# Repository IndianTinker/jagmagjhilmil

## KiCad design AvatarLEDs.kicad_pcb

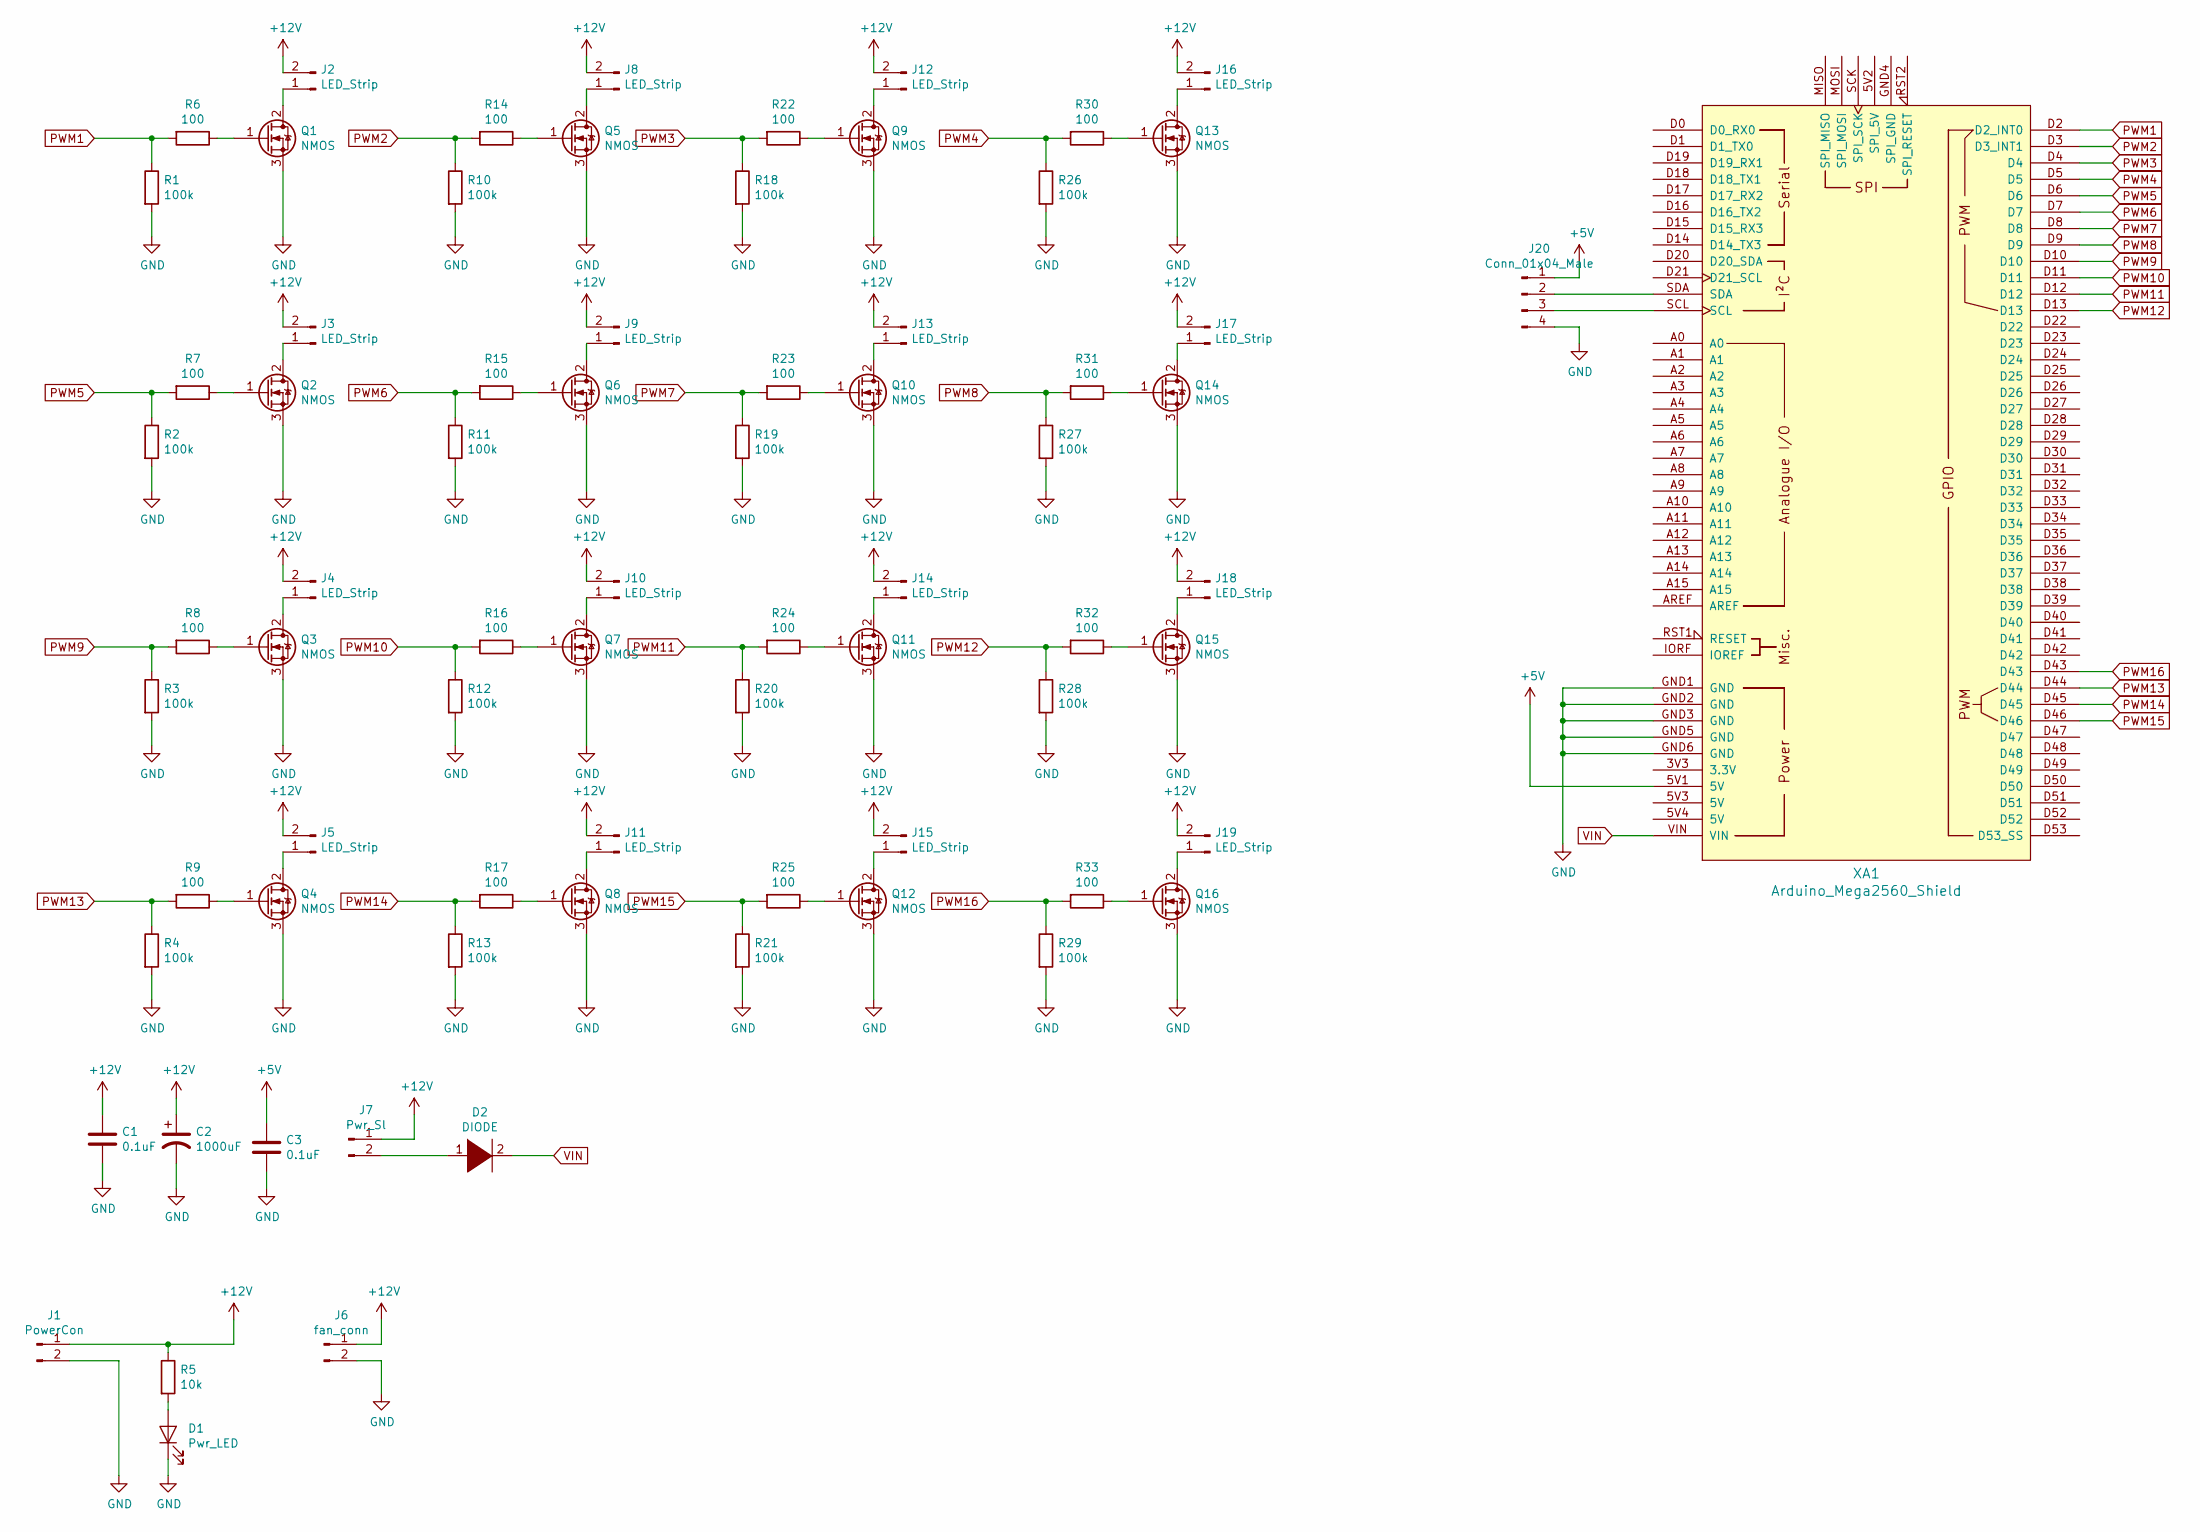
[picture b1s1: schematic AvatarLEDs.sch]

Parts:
C1, C3: 0.1uF; C_0805_2012Metric_Pad1.15x1.40mm_HandSolder
C2: 1000uF; CP_Elec_5x3
D1: Pwr_LED; LED_D3.0mm_FlatTop
D2: DIODE; Diode_Bridge_Round_D9.0mm
J1: PowerCon; TerminalBlock_Phoenix_MKDS-1,5-2_1x02_P5.00mm_Horizontal
J2, J3, J4, J5, J8, J9, J10, J11, J12, J13, J14, J15, J16, J17, J18, J19: LED_Strip; TerminalBlock_Phoenix_MKDS-1,5-2_1x02_P5.00mm_Horizontal
J6: fan_conn; JST_EH_B02B-EH-A_1x02_P2.50mm_Vertical
J7: Pwr_Sl; JST_EH_B02B-EH-A_1x02_P2.50mm_Vertical
J20: Conn_01x04_Male; JST_EH_B04B-EH-A_1x04_P2.50mm_Vertical
Q1, Q2, Q3, Q4, Q5, Q6, Q7, Q8, Q9, Q10, Q11, Q12, Q13, Q14, Q15, Q16: NMOS; TO-220-3_Vertical
R1, R2, R3, R4, R10, R11, R12, R13, R18, R19, R20, R21, R26, R27, R28, R29: 100k; R_1206_3216Metric_Pad1.42x1.75mm_HandSolder
R5: 10k; R_1206_3216Metric_Pad1.42x1.75mm_HandSolder
R6, R7, R8, R9, R14, R15, R16, R17, R22, R23, R24, R25, R30, R31, R32, R33: 100; R_1206_3216Metric_Pad1.42x1.75mm_HandSolder
XA1: Arduino_Mega2560_Shield

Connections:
+5V: C3.1, J20.1, XA1.5V1 (5V)
+12V: C1.1, C2.1, J1.1, J2.2, J3.2, J4.2, J5.2, J6.1, J7.1, J8.2, J9.2, J10.2, J11.2, J12.2, J13.2, J14.2, J15.2, J16.2, J17.2, J18.2, J19.2, R5.1
GND: C1.2, C2.2, C3.2, D1.1 (K), J1.2, J6.2, J20.4, Q1.3 (S), Q2.3 (S), Q3.3 (S), Q4.3 (S), Q5.3 (S), Q6.3 (S), Q7.3 (S), Q8.3 (S), Q9.3 (S), Q10.3 (S), Q11.3 (S), Q12.3 (S), Q13.3 (S), Q14.3 (S), Q15.3 (S), Q16.3 (S), R1.2, R2.2, R3.2, R4.2, R10.2, R11.2, R12.2, R13.2, R18.2, R19.2, R20.2, R21.2, R26.2, R27.2, R28.2, R29.2, XA1.GND1 (GND), XA1.GND2 (GND), XA1.GND3 (GND), XA1.GND5 (GND), XA1.GND6 (GND)
unnamed: D1.2 (A), R5.2
unnamed: D2.1 (K), J7.2
unnamed: J2.1, Q1.2 (D)
unnamed: J3.1, Q2.2 (D)
unnamed: J4.1, Q3.2 (D)
unnamed: J5.1, Q4.2 (D)
unnamed: J8.1, Q5.2 (D)
unnamed: J9.1, Q6.2 (D)
unnamed: J10.1, Q7.2 (D)
unnamed: J11.1, Q8.2 (D)
unnamed: J12.1, Q9.2 (D)
unnamed: J13.1, Q10.2 (D)
unnamed: J14.1, Q11.2 (D)
unnamed: J15.1, Q12.2 (D)
unnamed: J16.1, Q13.2 (D)
unnamed: J17.1, Q14.2 (D)
unnamed: J18.1, Q15.2 (D)
unnamed: J19.1, Q16.2 (D)
unnamed: J20.2, XA1.SDA
unnamed: J20.3, XA1.SCL
unnamed: Q1.1 (G), R6.1
unnamed: Q2.1 (G), R7.1
unnamed: Q3.1 (G), R8.1
unnamed: Q4.1 (G), R9.1
unnamed: Q5.1 (G), R14.1
unnamed: Q6.1 (G), R15.1
unnamed: Q7.1 (G), R16.1
unnamed: Q8.1 (G), R17.1
unnamed: Q9.1 (G), R22.1
unnamed: Q10.1 (G), R23.1
unnamed: Q11.1 (G), R24.1
unnamed: Q12.1 (G), R25.1
unnamed: Q13.1 (G), R30.1
unnamed: Q14.1 (G), R31.1
unnamed: Q15.1 (G), R32.1
unnamed: Q16.1 (G), R33.1
PWM1: R1.1, R6.2, XA1.D2 (D2_INT0)
PWM2: R10.1, R14.2, XA1.D3 (D3_INT1)
PWM3: R18.1, R22.2, XA1.D4
PWM4: R26.1, R30.2, XA1.D5
PWM5: R2.1, R7.2, XA1.D6
PWM6: R11.1, R15.2, XA1.D7
PWM7: R19.1, R23.2, XA1.D8
PWM8: R27.1, R31.2, XA1.D9
PWM9: R3.1, R8.2, XA1.D10
PWM10: R12.1, R16.2, XA1.D11
PWM11: R20.1, R24.2, XA1.D12
PWM12: R28.1, R32.2, XA1.D13
PWM13: R4.1, R9.2, XA1.D44
PWM14: R13.1, R17.2, XA1.D45
PWM15: R21.1, R25.2, XA1.D46
PWM16: R29.1, R33.2, XA1.D43
VIN: D2.2 (A), XA1.VIN

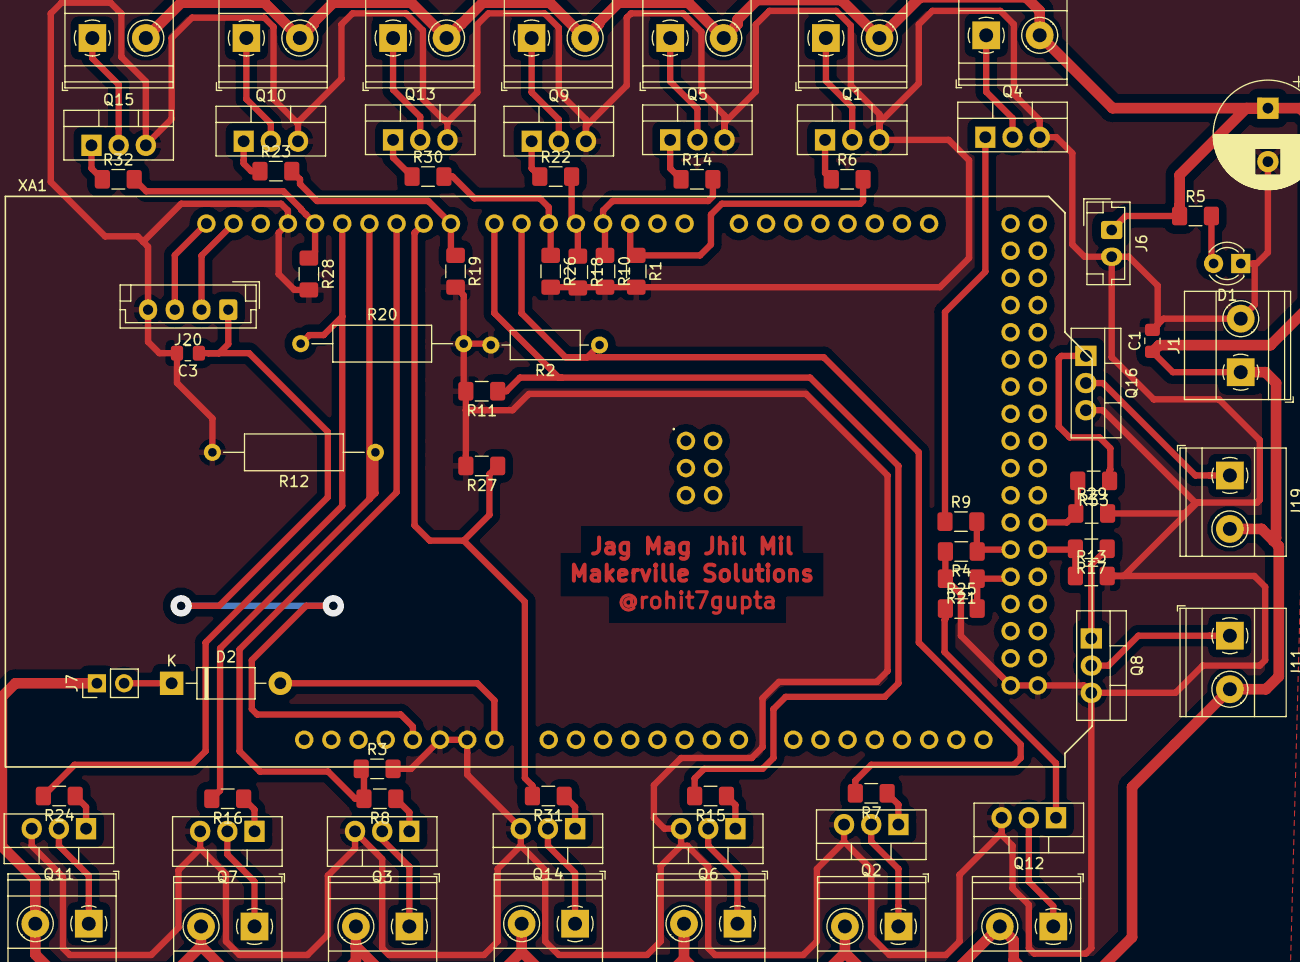
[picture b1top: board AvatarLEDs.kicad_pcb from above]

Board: 2 copper layers, 75 parts (0 on the bottom side), 56 nets.

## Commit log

2019-04-11 rokda
